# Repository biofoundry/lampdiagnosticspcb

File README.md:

# lampdiagnosticspcb
PCB Design for the LAMP Diagnostics device. Datasheets can be found in the Datasheet folder.

 My frist KiCAD project, sorry for any errors!

Based on a device built by Frank B. Myers, Richard H. Henrikson,Jennifer Bone and Luke P. Lee

http://journals.plos.org/plosone/article?id=10.1371/journal.pone.0070266
https://github.com/fbmyers/MicroBAR

This is a collaborative effort from bioHack Sydney and BioFoundry. 

Teensy's ADC / Voltage Reference
----------------

https://forum.pjrc.com/threads/27198-Using-External-AREF-with-ADC/page2

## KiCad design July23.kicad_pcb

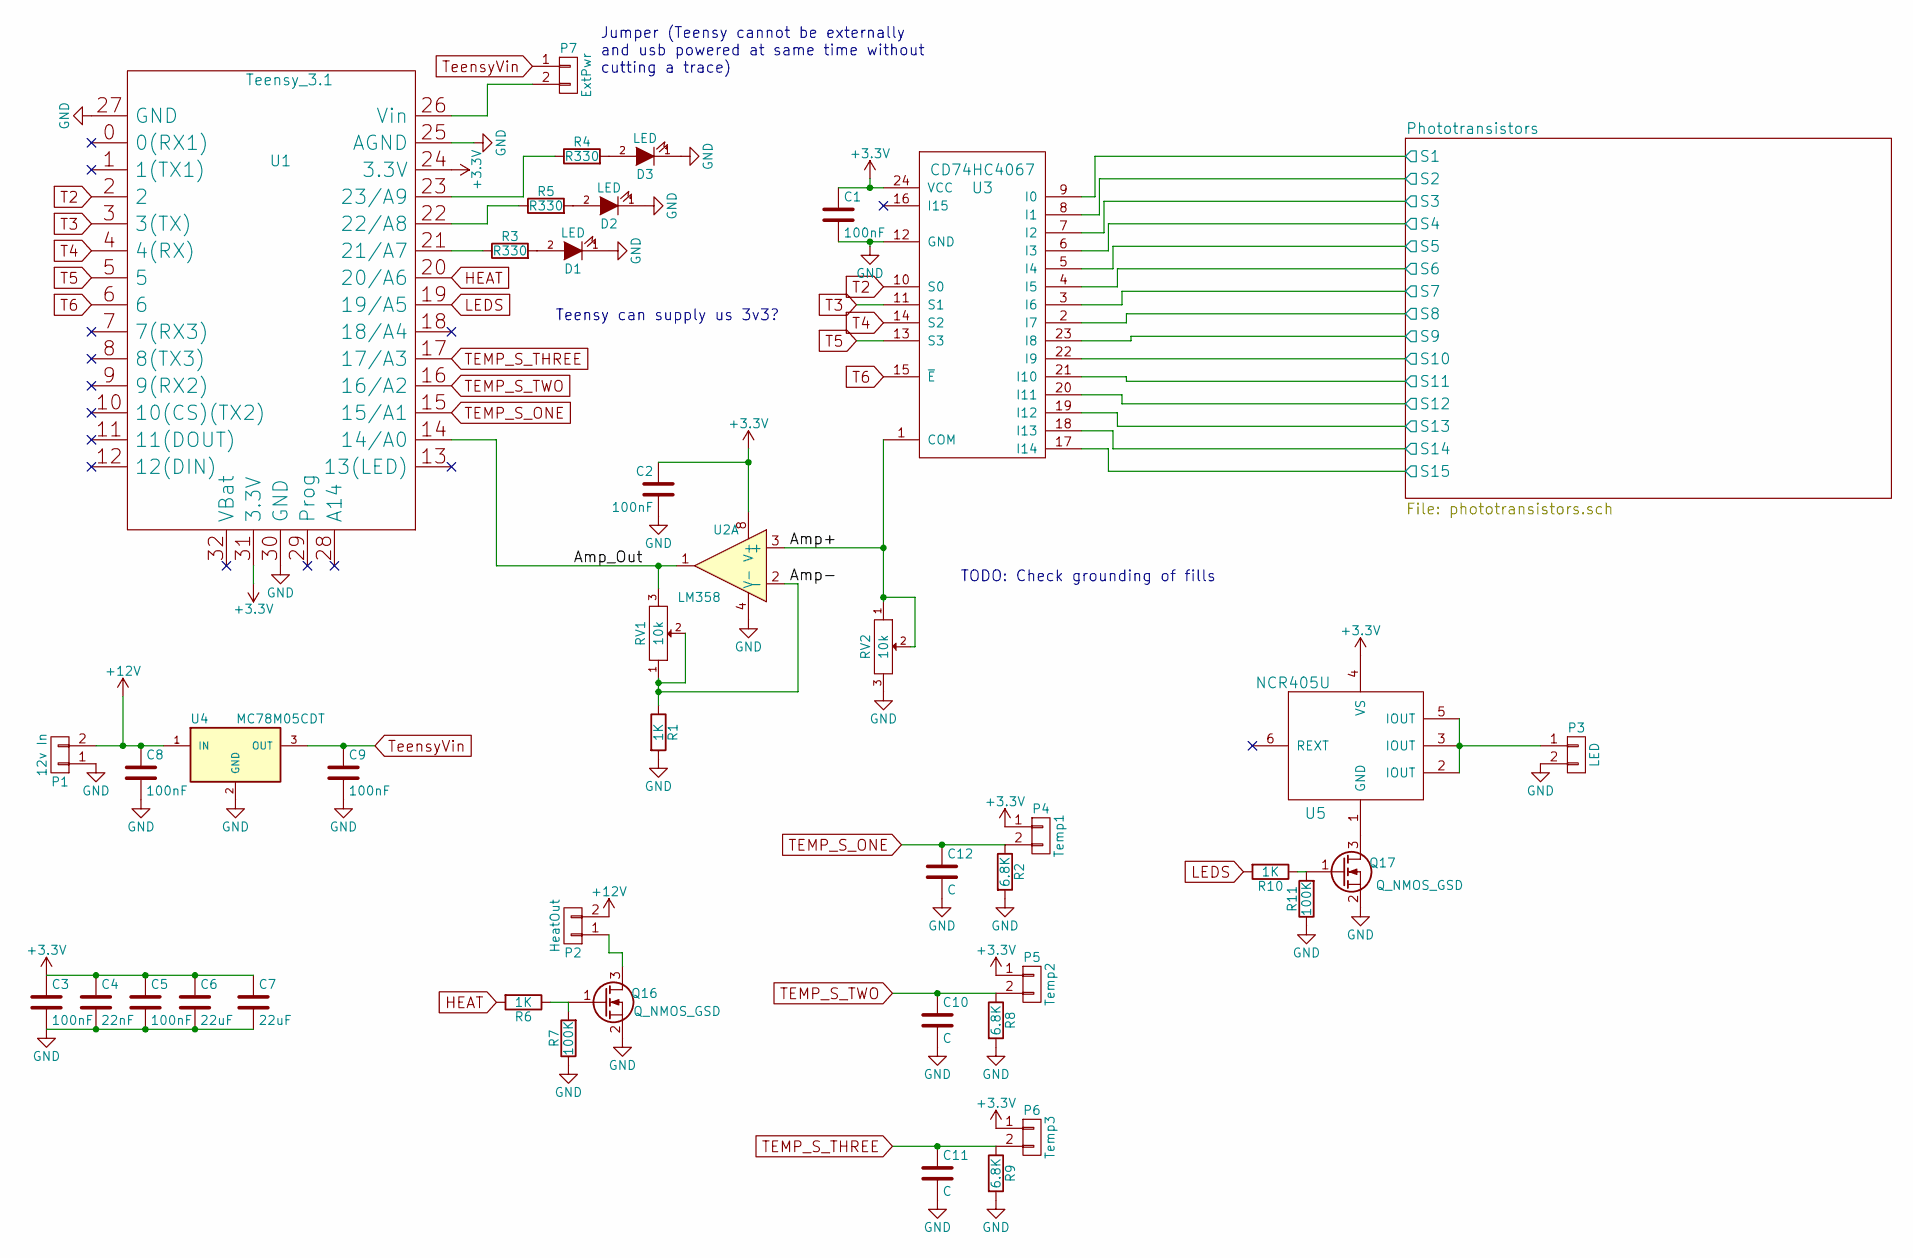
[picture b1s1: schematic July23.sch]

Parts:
C1, C2, C3, C5, C8, C9: 100nF; C_0805_HandSoldering
C4: 22nF; C_0805_HandSoldering
C6, C7: 22uF; C_0805_HandSoldering
C10, C11, C12: C; C_0805_HandSoldering
D1, D2, D3: LED; LED_0805
P1: 12v In; 2_5mm_screw_terminal
P2: HeatOut; 2_5mm_screw_terminal
P3: LED; 2_5mm_screw_terminal
P4: Temp1; 2_5mm_screw_terminal
P5: Temp2; 2_5mm_screw_terminal
P6: Temp3; 2_5mm_screw_terminal
P7: ExtPwr; Pin_Header_Straight_1x02
Q16, Q17: Q_NMOS_GSD; SOT-23_Handsoldering
R1, R6, R10: 1K; R_0805_HandSoldering
R2, R8, R9: 6.8K; R_0805_HandSoldering
R3, R4, R5: R330; R_0805_HandSoldering
R7, R11: 100K; R_0805_HandSoldering
RV1, RV2: 10k; Potentiometer_Trimmer-Suntan-TSR-3386P
U1: Teensy_3.1; Teensy-3.1
U2: LM358; DIP-8_W7.62mm
U3: CD74HC4067; DIP-24_W10.16mm
U4: MC78M05CDT; TO-252-2Lead
U5: NCR405U; SOT457

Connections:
+3V3: C1.1, C2.1, C3.1, C4.1, C5.1, C6.1, C7.1, P4.1, P5.1, P6.1, U1.24 (3.3V), U1.31 (3.3V), U2.8 (V+), U3.24 (VCC), U5.4 (VS); also elsewhere on the board
+12V: C8.1, P1.2, P2.2, U4.1 (IN)
/Amp+: RV2.1, RV2.2, U2.3 (+), U3.1 (COM)
/Amp-: R1.1, RV1.1, RV1.2, U2.2 (-)
/Amp_Out: RV1.3, U1.14 (14/A0), U2.1
/Phototransistors/S1: U3.9 (I0); also elsewhere on the board
/Phototransistors/S2: U3.8 (I1); also elsewhere on the board
/Phototransistors/S3: U3.7 (I2); also elsewhere on the board
/Phototransistors/S4: U3.6 (I3); also elsewhere on the board
/Phototransistors/S5: U3.5 (I4); also elsewhere on the board
/Phototransistors/S6: U3.4 (I5); also elsewhere on the board
/Phototransistors/S7: U3.3 (I6); also elsewhere on the board
/Phototransistors/S8: U3.2 (I7); also elsewhere on the board
/Phototransistors/S9: U3.23 (I8); also elsewhere on the board
/Phototransistors/S10: U3.22 (I9); also elsewhere on the board
/Phototransistors/S11: U3.21 (I10); also elsewhere on the board
/Phototransistors/S12: U3.20 (I11); also elsewhere on the board
/Phototransistors/S13: U3.19 (I12); also elsewhere on the board
/Phototransistors/S14: U3.18 (I13); also elsewhere on the board
/Phototransistors/S15: U3.17 (I14); also elsewhere on the board
GND: C1.2, C2.2, C3.2, C4.2, C5.2, C6.2, C7.2, C8.2, C9.2, C10.2, C11.2, C12.2, D1.1 (K), D2.1 (K), D3.1 (K), P1.1, P3.2, Q16.2 (S), Q17.2 (S), R1.2, R2.2, R7.1, R8.2, R9.2, R11.1, RV2.3, U1.25 (AGND), U1.27 (GND), U1.30 (GND), U2.4 (V-), U3.12 (GND), U4.2 (GND)
HEAT: R6.2, U1.20 (20/A6)
LEDS: R10.2, U1.19 (19/A5)
unnamed: D1.2 (A), R3.2
unnamed: D2.2 (A), R5.2
unnamed: D3.2 (A), R4.2
unnamed: P2.1, Q16.3 (D)
unnamed: P3.1, U5.2 (IOUT), U5.3 (IOUT), U5.5 (IOUT)
unnamed: P7.2, U1.26 (Vin)
unnamed: Q16.1 (G), R6.1, R7.2
unnamed: Q17.1 (G), R10.1, R11.2
unnamed: Q17.3 (D), U5.1 (GND)
unnamed: R3.1, U1.21 (21/A7)
unnamed: R4.1, U1.23 (23/A9)
unnamed: R5.1, U1.22 (22/A8)
unnamed: U2.6 (-), U2.7
T2: U1.2, U3.10 (S0)
T3: U1.3 (3(TX)), U3.11 (S1)
T4: U1.4 (4(RX)), U3.14 (S2)
T5: U1.5, U3.13 (S3)
T6: U1.6, U3.15 (~E)
TEMP_S_ONE: C12.1, P4.2, R2.1, U1.15 (15/A1)
TEMP_S_THREE: C11.1, P6.2, R9.1, U1.17 (17/A3)
TEMP_S_TWO: C10.1, P5.2, R8.1, U1.16 (16/A2)
TeensyVin: C9.1, P7.1, U4.3 (OUT)

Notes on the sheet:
Jumper (Teensy cannot be externally and usb powered at same time without cutting a trace)
Teensy can supply us 3v3?
TODO: Check grounding of fills

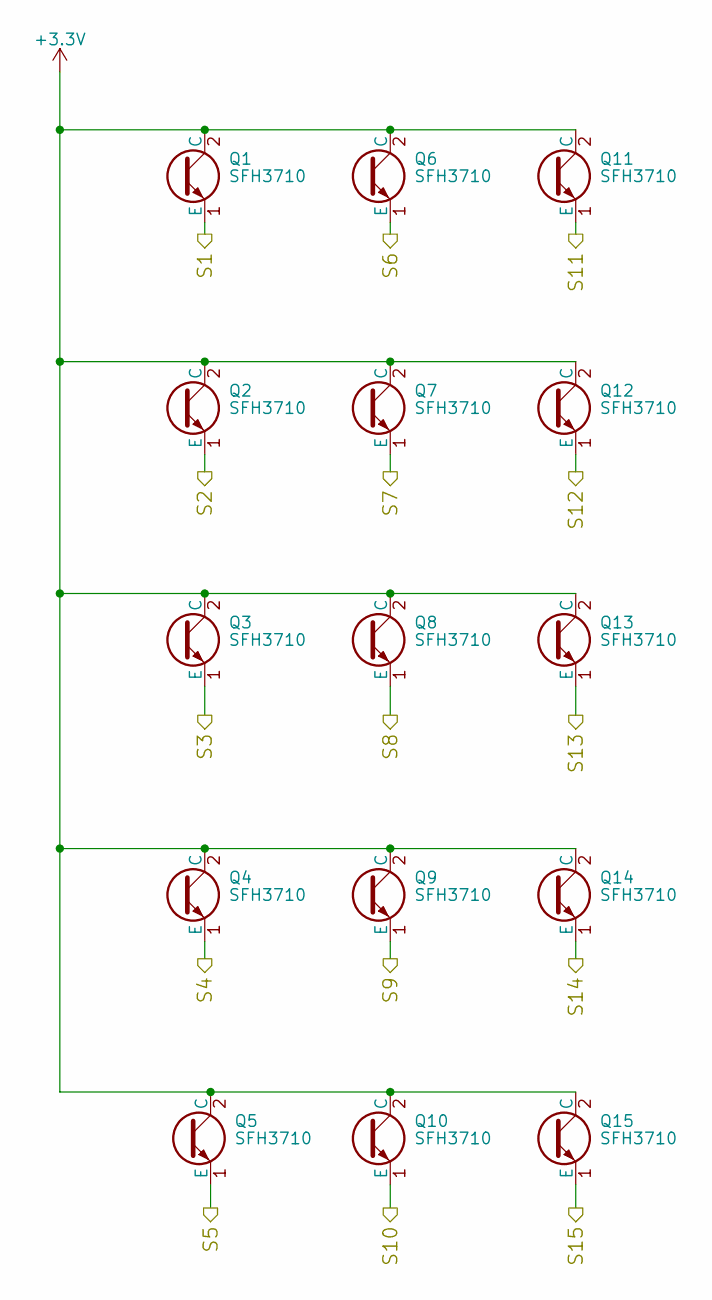
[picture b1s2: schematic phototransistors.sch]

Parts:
Q1, Q2, Q3, Q4, Q5, Q6, Q7, Q8, Q9, Q10, Q11, Q12, Q13, Q14, Q15: SFH3710; R_0805_HandSoldering

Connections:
+3V3: Q1.2 (C), Q2.2 (C), Q3.2 (C), Q4.2 (C), Q5.2 (C), Q6.2 (C), Q7.2 (C), Q8.2 (C), Q9.2 (C), Q10.2 (C), Q11.2 (C), Q12.2 (C), Q13.2 (C), Q14.2 (C), Q15.2 (C); also elsewhere on the board
/Phototransistors/S1: Q1.1 (E); also elsewhere on the board
/Phototransistors/S2: Q2.1 (E); also elsewhere on the board
/Phototransistors/S3: Q3.1 (E); also elsewhere on the board
/Phototransistors/S4: Q4.1 (E); also elsewhere on the board
/Phototransistors/S5: Q5.1 (E); also elsewhere on the board
/Phototransistors/S6: Q6.1 (E); also elsewhere on the board
/Phototransistors/S7: Q7.1 (E); also elsewhere on the board
/Phototransistors/S8: Q8.1 (E); also elsewhere on the board
/Phototransistors/S9: Q9.1 (E); also elsewhere on the board
/Phototransistors/S10: Q10.1 (E); also elsewhere on the board
/Phototransistors/S11: Q11.1 (E); also elsewhere on the board
/Phototransistors/S12: Q12.1 (E); also elsewhere on the board
/Phototransistors/S13: Q13.1 (E); also elsewhere on the board
/Phototransistors/S14: Q14.1 (E); also elsewhere on the board
/Phototransistors/S15: Q15.1 (E); also elsewhere on the board

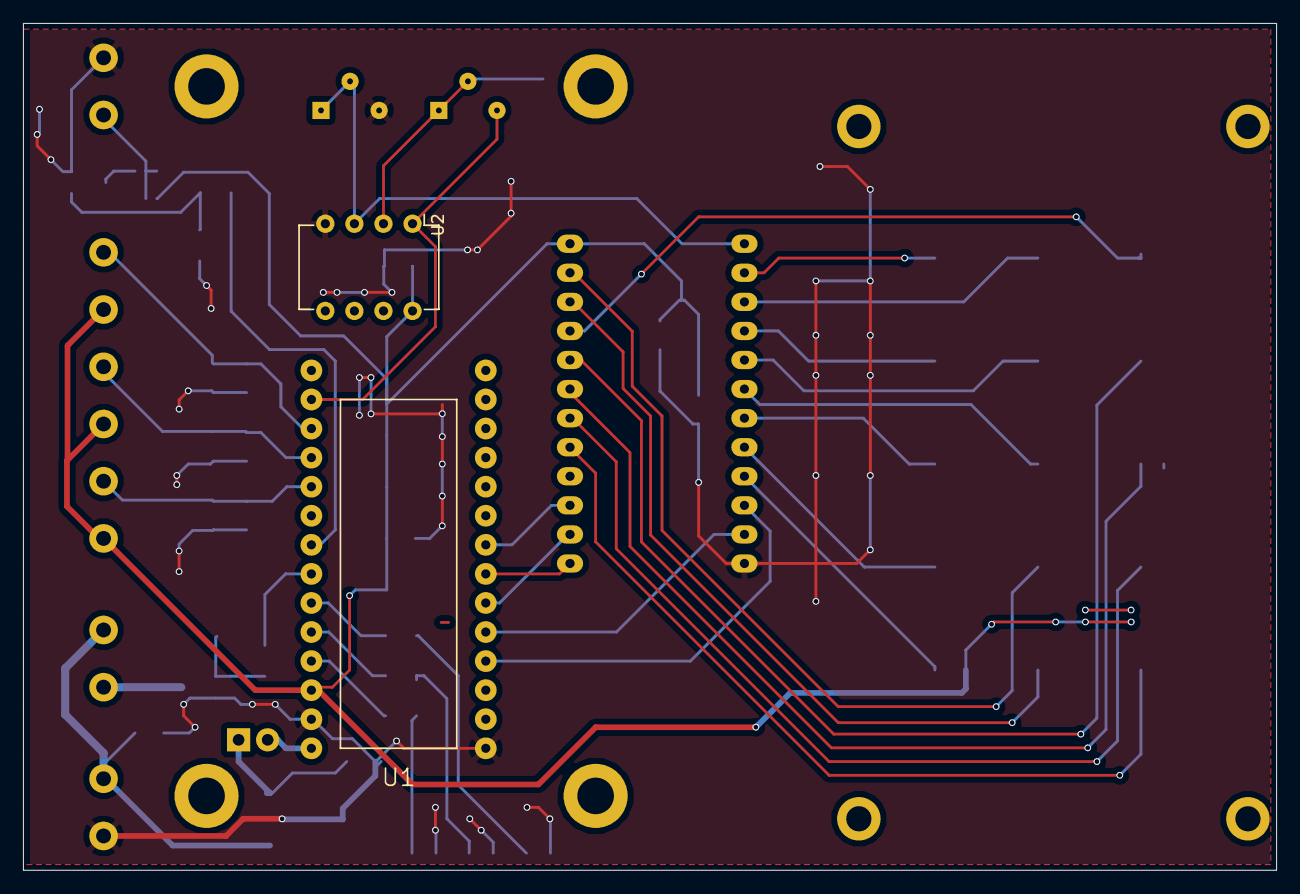
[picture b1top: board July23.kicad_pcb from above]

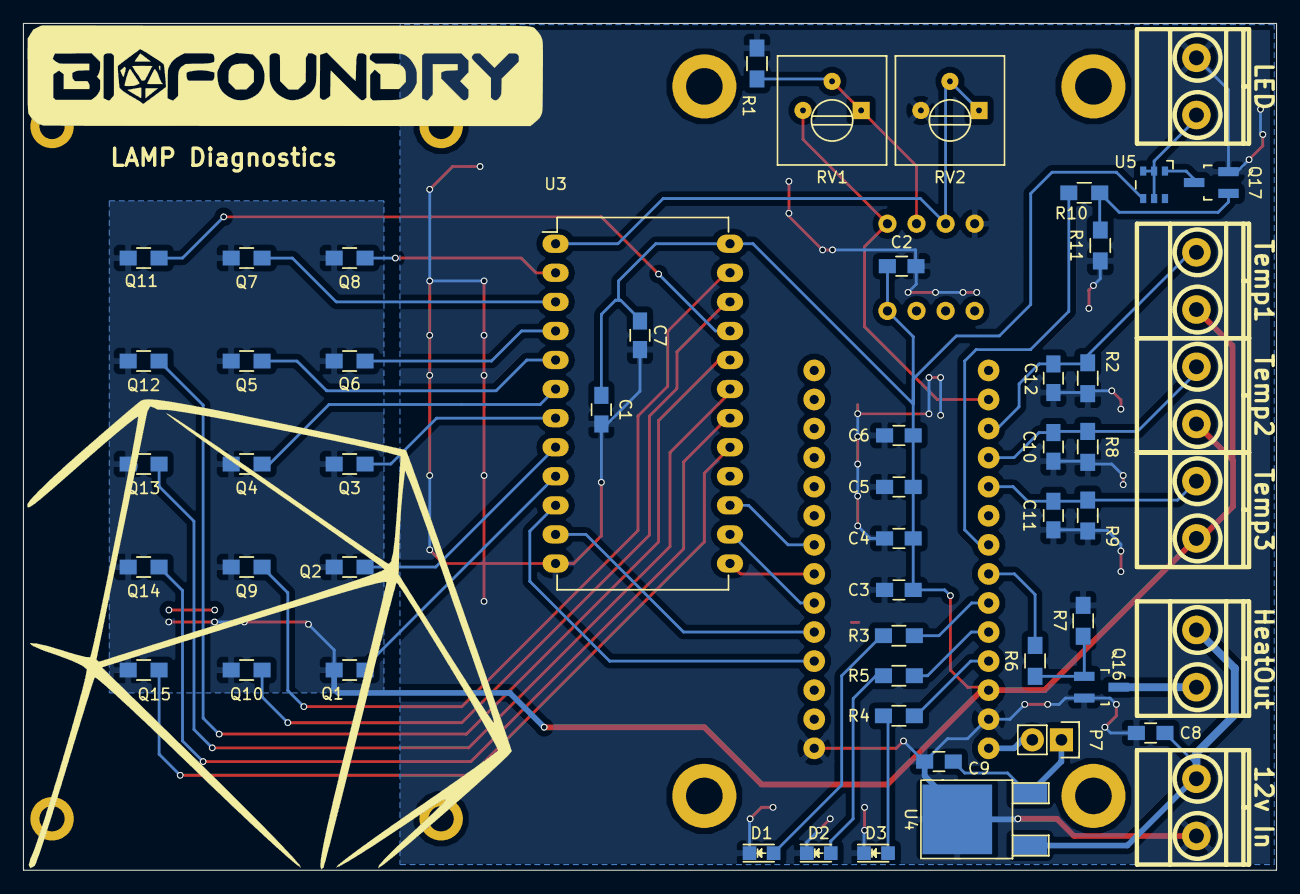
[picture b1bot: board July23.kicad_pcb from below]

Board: 2 copper layers, 109.5 x 74.0 mm, 57 parts (55 on the bottom side), 45 nets.

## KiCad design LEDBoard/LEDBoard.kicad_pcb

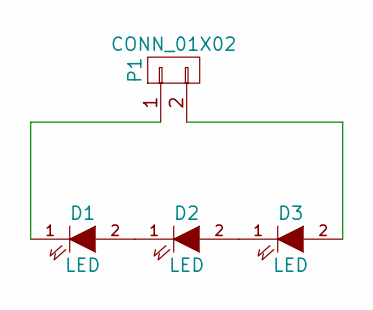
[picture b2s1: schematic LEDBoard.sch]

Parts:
D1, D2, D3: LED; LED-5MM
P1: CONN_01X02; Pin_Header_Straight_1x02

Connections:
unnamed: D1.1 (K), P1.1
unnamed: D1.2 (A), D2.1 (K)
unnamed: D2.2 (A), D3.1 (K)
unnamed: D3.2 (A), P1.2

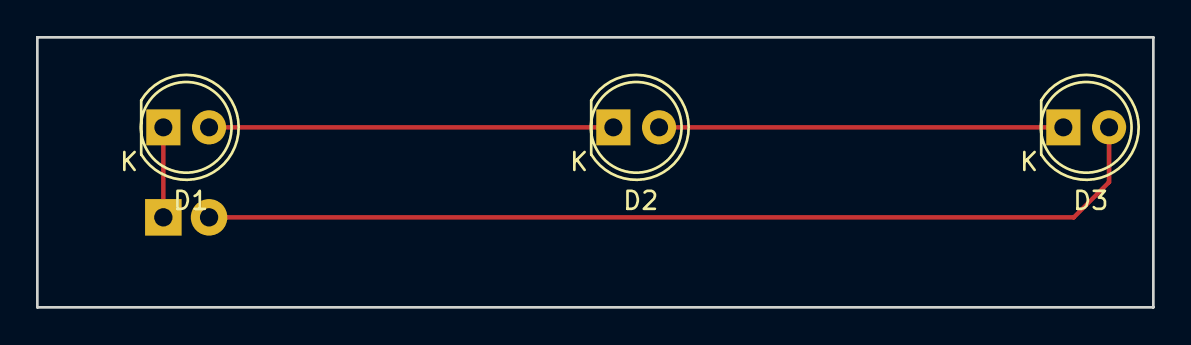
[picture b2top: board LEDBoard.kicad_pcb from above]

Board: 2 copper layers, 62.0 x 15.0 mm, 4 parts (1 on the bottom side), 4 nets.

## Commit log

2016-02-09 Created project file
2016-02-09 New footprint for teensy
2016-02-09 Part?
2016-02-09 Datasheets are useful. Because Data.
2016-02-09 Data
2016-02-09 Datasheet
2016-02-09 schematic so far
2016-02-09 Progress on schematic, phototransistor array + analog frontend complete
2016-02-09 Datasheets
2016-02-09 LEDBoard
2016-02-09 Draft version v1 of Schematic
2016-02-11 Board design V1
2016-02-11 BoardV2
2016-02-20 Added breakout headers for phototransistors, added GNDA for analog aspects
2016-02-24 Changed VIN --> 3.3v, analog GND to AGND, added 3 status LED's
2016-02-24 PCB furtherererd
2016-03-11 VERSION ONE - Sent for manufacturegit add -Agit add -A
2016-07-19 Added missing pot, logos and mounting holes.
2016-07-19 Deleted Redundant
2016-07-19 Deleted redundant files. July 18 Pro / Board files are latest. Next step is firmware
2016-07-19 Silkscreening
2016-07-19 More via stitching, more bypass for mux
2016-07-19 MountHoles
2016-07-19 Blarg, KiCAD crashed, redoing all before, repushing often
2016-07-21 Big revamp
    Added mosfet to LED output
    Changed LED driver to NCR405U
    Changed phototransistor array to be 9mm * 9mm to match standard 96 well
    sizing
    Added 5v Linear reg to feed the teensy as well as a jumper so we can do
    initial tests using usb power
2016-07-21 Added Name ^.^
2016-07-22 Moved via ^.^
2016-07-23 Cleaned up Old files
2016-07-23 Changed schematic of SFH3710
2016-07-23 OpAmp circuit needs checking
2016-07-26 opamp flipped for clarity
2016-07-26 fixing up opamp on PCB (work in progress)
2016-07-28 improved Gnd stitching
    unused part of LM358 still to be connected somewhere
2016-07-30 bigger 3v3 tracks
    not sure if LED supply is better or worse now - it's away from the opamp (that's good), but now might cause interference on the temp. sensors (that's bad).
    If LED isn't switched much, and/or if temperature accuracy isn't critical, this layout should be OK.
    Might still be worth moving some of the 3v3 capacitors over to the phototransistors though.
